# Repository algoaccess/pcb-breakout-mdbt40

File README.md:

# pcb-breakout-mdbt40
Pin breakout of the Raytac MDBT40 module based on Nordic NRF51 to through-hole pin headers for prototyping.

##PCB Design software and addons used

1. Eagle 7.3.0 standard
2. MDBT40 library by [bluzDK](https://github.com/bluzDK/bluzDK) (in repo as MDBT40-v2-bluzDK)

##Images

This is the older revision 1 design. It has an error of the pin header not being directly suitable for the breadboard without some forcing. Corrected in Revision 2.

##Schematic drawings
Images are exported from Eagle at 600dpi.

##Parts required

The MDBT40 module can be bought direct from the manufacturer [Raytac](http://www.raytac.com/)

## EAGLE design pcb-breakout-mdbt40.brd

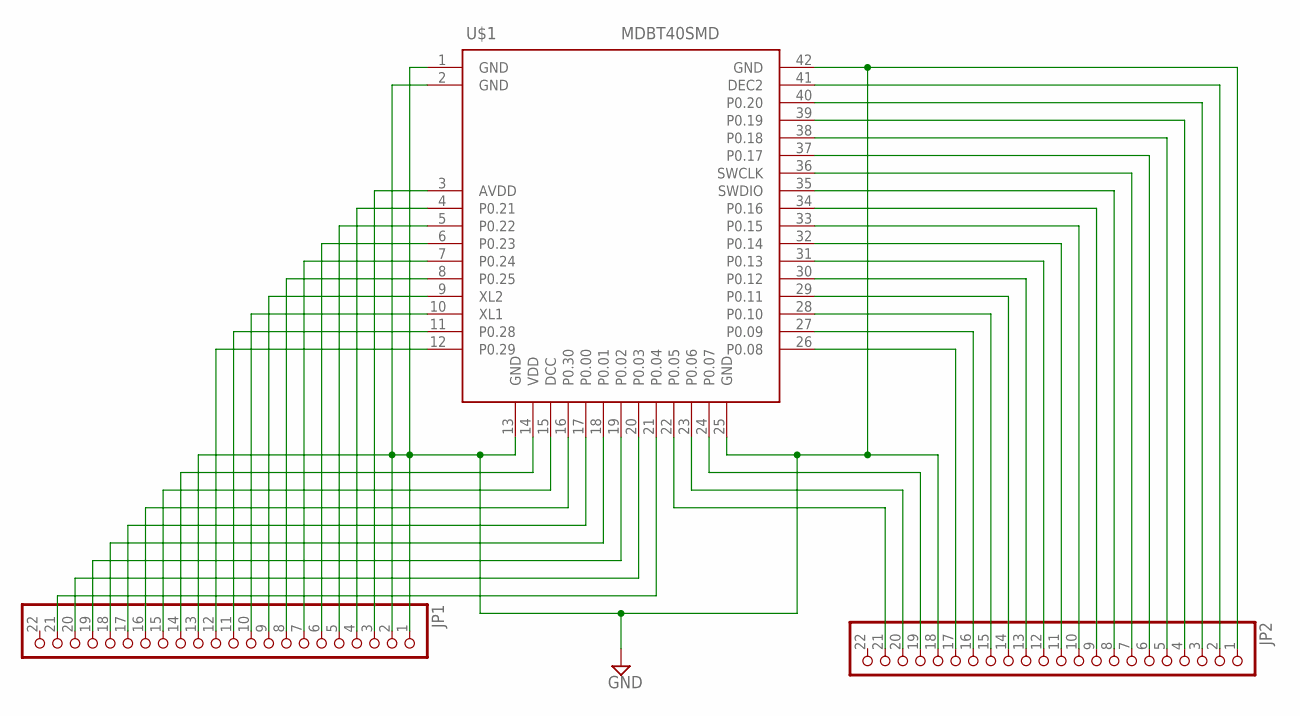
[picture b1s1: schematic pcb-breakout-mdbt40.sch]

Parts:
JP1, JP2: PINHD-1X22; 1X22
U$1: MDBT40SMD; MDBT40

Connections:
GND: JP1.1, JP1.2, JP1.13, JP2.1, JP2.18, U$1.1 (GND), U$1.2 (GND), U$1.13 (GND), U$1.25 (GND), U$1.42 (GND)
unnamed: JP1.3, U$1.3 (AVDD)
unnamed: JP1.4, U$1.4 (P0.21)
unnamed: JP1.5, U$1.5 (P0.22)
unnamed: JP1.6, U$1.6 (P0.23)
unnamed: JP1.7, U$1.7 (P0.24)
unnamed: JP1.8, U$1.8 (P0.25)
unnamed: JP1.9, U$1.9 (XL2)
unnamed: JP1.10, U$1.10 (XL1)
unnamed: JP1.11, U$1.11 (P0.28)
unnamed: JP1.12, U$1.12 (P0.29)
unnamed: JP1.14, U$1.14 (VDD)
unnamed: JP1.15, U$1.15 (DCC)
unnamed: JP1.16, U$1.16 (P0.30)
unnamed: JP1.17, U$1.17 (P0.00)
unnamed: JP1.18, U$1.18 (P0.01)
unnamed: JP1.19, U$1.19 (P0.02)
unnamed: JP1.20, U$1.20 (P0.03)
unnamed: JP1.21, U$1.21 (P0.04)
unnamed: JP2.2, U$1.41 (DEC2)
unnamed: JP2.3, U$1.40 (P0.20)
unnamed: JP2.4, U$1.39 (P0.19)
unnamed: JP2.5, U$1.38 (P0.18)
unnamed: JP2.6, U$1.37 (P0.17)
unnamed: JP2.7, U$1.36 (SWCLK)
unnamed: JP2.8, U$1.35 (SWDIO)
unnamed: JP2.9, U$1.34 (P0.16)
unnamed: JP2.10, U$1.33 (P0.15)
unnamed: JP2.11, U$1.32 (P0.14)
unnamed: JP2.12, U$1.31 (P0.13)
unnamed: JP2.13, U$1.30 (P0.12)
unnamed: JP2.14, U$1.29 (P0.11)
unnamed: JP2.15, U$1.28 (P0.10)
unnamed: JP2.16, U$1.27 (P0.09)
unnamed: JP2.17, U$1.26 (P0.08)
unnamed: JP2.19, U$1.24 (P0.07)
unnamed: JP2.20, U$1.23 (P0.06)
unnamed: JP2.21, U$1.22 (P0.05)

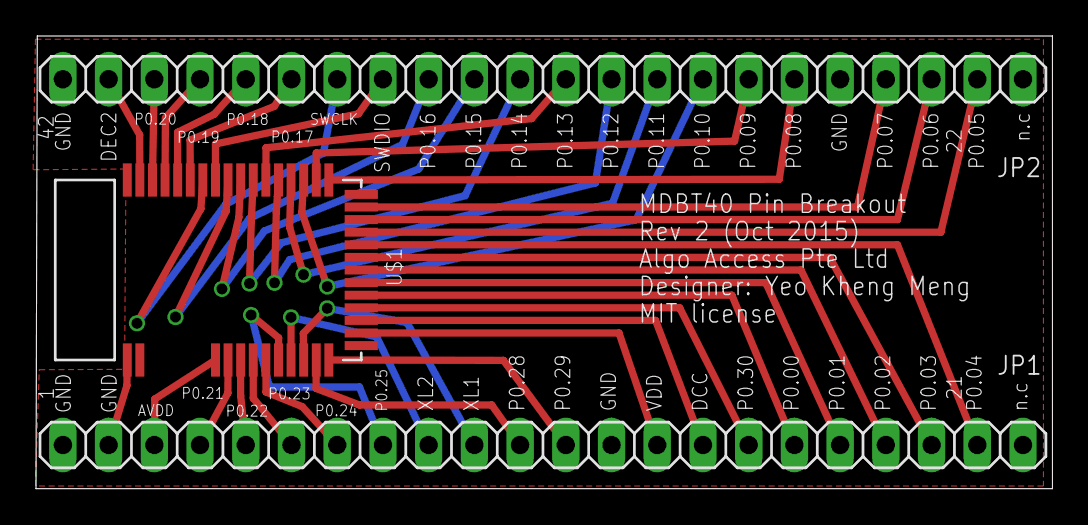
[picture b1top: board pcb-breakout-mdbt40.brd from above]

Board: 2 copper layers, 56.5 x 25.1 mm, 3 parts (0 on the bottom side), 38 nets.

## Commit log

2015-10-20 pin number
2015-10-20 rev 1 gerbil
2015-10-20 some silkscreen position
2015-10-20 connect ground plane
2015-10-20 prevent via short circuit
2015-10-20 new rev 1 gerbil
2015-10-27 enlarged board width and shifting JP2
2015-10-27 clearance issues
2015-10-27 adjust ground plane
2015-10-27 images and rev2 gerbels
2015-10-27 permissions issues on windows
2015-10-27 front image

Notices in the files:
pcb-breakout-mdbt40.brd:
MIT license
